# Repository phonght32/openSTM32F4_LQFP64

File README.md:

# openSTM32F4_LQFP64

### 1. Overview

Everything about this board: schematic, PCB gerber and BOM are free to distribute under open-source license for users.

The STM32F4 series chip inside openSTM32 board is based on ARM Cortex-M4 with floating point unit (FPU).

### 2. Specifications

| Items               | Specifications                                               |
| ------------------- | ------------------------------------------------------------ |
| Power supply        | 5V micro USB<br />5~36V Jack DC                              |
| Microcontroller     | STM32F405RGT6 / 32-bit ARM Cortex-M4 with FPU(168MHz, 225DMIPS) |
| Sensors             | 3 axis gyroscope, 3 axis accelerometer, 3 axis magnetometer (MPU9250) |
| Programmer          | JTAG/SWD connector<br />Serial (UART3)                       |
| Communicaton Ports  | UART x 3<br />I2C x 1<br />SPI x 1                           |
| Multimedia          | I2S x 1                                                      |
| Analog input        | ADC channel x 5                                              |
| Analog output       | DAC channel x 1                                              |
| PWM                 | Timer PWM x 4                                                |
| Leds and buttons    | D7 and D8: USB communication<br />D6: 3V3 power on<br />D1: USER LED status<br />SW2: Reset button<br />SW1: USER button |
| Digital I/O         | 10 pins                                                      |
| Output power source | 5V max 3A (TPS5430 step-down converter)<br />3V3 max 1A (AMS1117 linear regulator) |
| Dimensions          | 68 x 64 mm                                                   |

**NOTE:**

This board auto select power supply when both USB and jackDC are powered.

### 3. Layout / Pin map

### 4. Hardware design

#### Schematic

#### Dimension

#### PCB Top

#### PCB Bot

#### 3D Top

#### 3D Bot

### 5. Bill of Materials (BOM)

Download BOM [here.](assets/bom.xlsx)

### 6. Gerber

Download PCB gerber [here.](assets/openSTM32_68x54mm.zip)

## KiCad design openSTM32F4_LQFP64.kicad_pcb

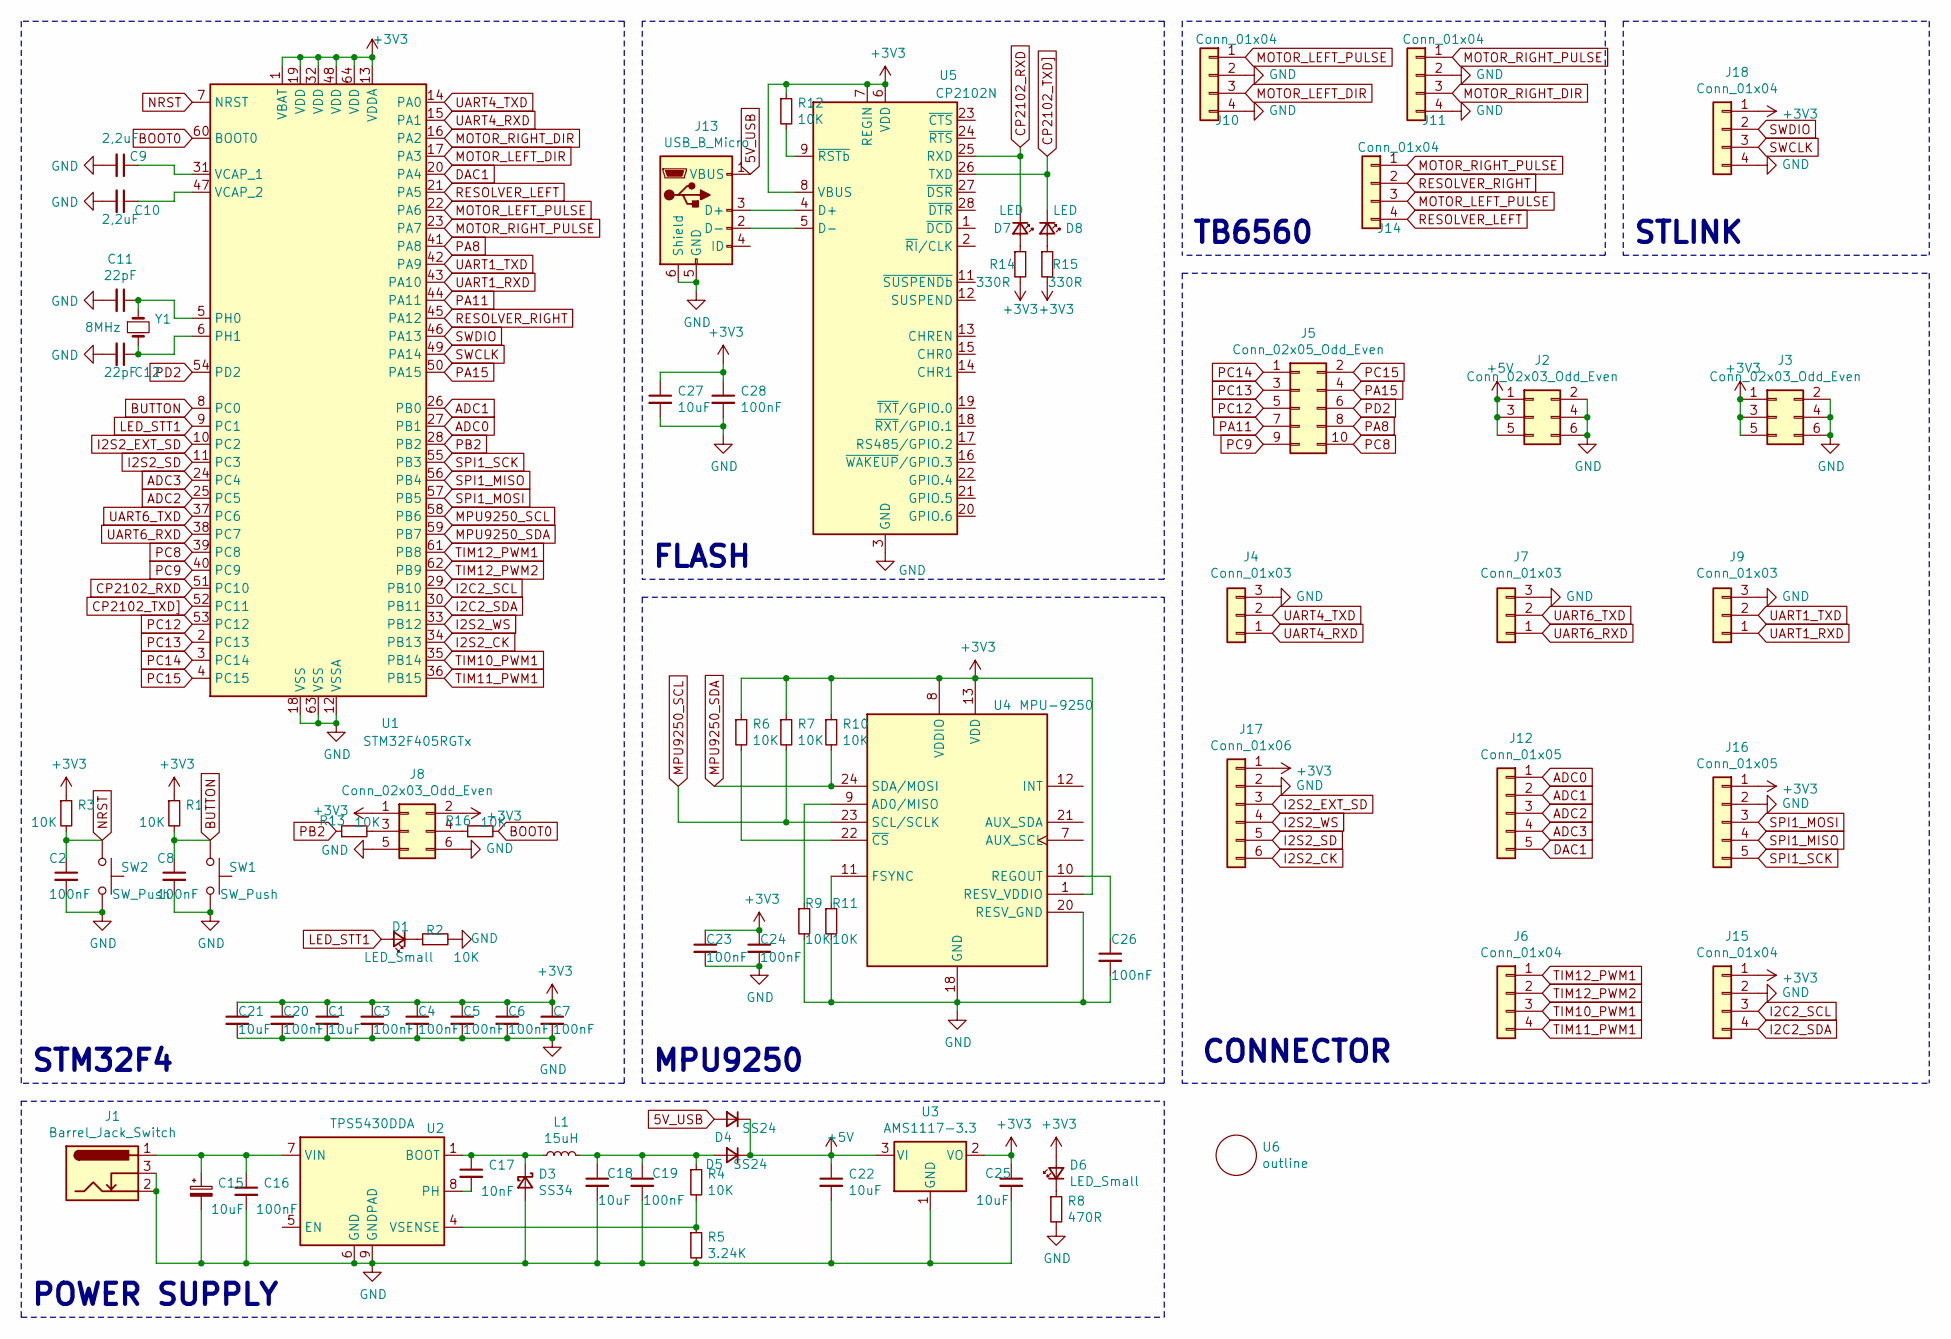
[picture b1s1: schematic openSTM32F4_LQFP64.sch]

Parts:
C1, C21, C22, C27: 10uF; C_0603_1608Metric_Pad1.05x0.95mm_HandSolder
C2, C3, C4, C5, C6, C7, C8, C16, C19, C20, C23, C24, C26, C28: 100nF; C_0603_1608Metric_Pad1.05x0.95mm_HandSolder
C9, C10: 2,2uF; C_0603_1608Metric_Pad1.05x0.95mm_HandSolder
C11, C12: 22pF; C_0603_1608Metric_Pad1.05x0.95mm_HandSolder
C15: 10uF; CP_Elec_8x10
C17: 10nF; C_0603_1608Metric_Pad1.05x0.95mm_HandSolder
C18, C25: 10uF; C_1210_3225Metric
D1, D6: LED_Small; LED_0603_1608Metric_Pad1.05x0.95mm_HandSolder
D3: SS34; D_SMA
D4, D5: SS24; D_SMA
D7, D8: LED; LED_0603_1608Metric_Pad1.05x0.95mm_HandSolder
J1: Barrel_Jack_Switch; BarrelJack_Wuerth_6941xx301002
J2, J3, J8: Conn_02x03_Odd_Even; PinHeader_2x03_P2.54mm_Vertical
J4, J7, J9: Conn_01x03; JST_EH_B3B-EH-A_1x03_P2.50mm_Vertical
J5: Conn_02x05_Odd_Even; PinHeader_2x05_P2.54mm_Vertical
J6, J10, J11, J15: Conn_01x04; JST_EH_B4B-EH-A_1x04_P2.50mm_Vertical
J12, J16: Conn_01x05; JST_EH_B5B-EH-A_1x05_P2.50mm_Vertical
J13: USB_B_Micro; USB_Micro-B_Wuerth_629105150521
J14, J18: Conn_01x04; PinHeader_1x04_P2.54mm_Vertical
J17: Conn_01x06; JST_EH_B6B-EH-A_1x06_P2.50mm_Vertical
L1: 15uH; L_12x12mm_H6mm
R1, R2, R3, R4, R6, R7, R9, R10, R11, R12, R13, R16: 10K; R_0603_1608Metric_Pad1.05x0.95mm_HandSolder
R5: 3.24K; R_0603_1608Metric_Pad1.05x0.95mm_HandSolder
R8: 470R; R_0603_1608Metric_Pad1.05x0.95mm_HandSolder
R14, R15: 330R; R_0603_1608Metric_Pad1.05x0.95mm_HandSolder
SW1, SW2: SW_Push; SW_Push_1P1T_NO_6x6mm_H9.5mm
U1: STM32F405RGTx; LQFP-64_10x10mm_P0.5mm
U2: TPS5430DDA; TI_SO-PowerPAD-8_ThermalVias
U3: AMS1117-3.3; SOT-223-3_TabPin2
U4: MPU-9250; MPU9250
U5: CP2102N; QFN-28-1EP_5x5mm_P0.5mm_EP3.35x3.35mm
U6: outline; openSTM32F4_LQFP64_outline
Y1: 8MHz; Crystal_HC49-4H_Vertical

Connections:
5V_USB: D4.2 (A), J13.1 (VBUS)
+3V3: C1.1, C3.1, C4.1, C5.1, C6.1, C7.1, C20.1, C21.1, C23.1, C24.1, C25.1, C27.1, C28.1, D6.2 (A), J3.1, J3.3, J3.5, J8.1, J8.2, J15.1, J16.1, J17.1, J18.1, R1.1, R3.1, R6.1, R7.1, R10.1, R12.1, R14.2, R15.2, U1.1 (VBAT), U1.13 (VDDA), U1.19 (VDD), U1.32 (VDD), U1.48 (VDD), U1.64 (VDD), U3.2 (VO), U4.1 (RESV_VDDIO), U4.8 (VDDIO), U4.13 (VDD), U5.6 (VDD), U5.7 (REGIN), U5.8 (VBUS)
+5V: C22.1, D4.1 (K), D5.1 (K), J2.1, J2.3, J2.5, U3.3 (VI)
ADC0: J12.1, U1.27 (PB1)
ADC1: J12.2, U1.26 (PB0)
ADC2: J12.3, U1.25 (PC5)
ADC3: J12.4, U1.24 (PC4)
BOOT0: R16.2, U1.60 (BOOT0)
BUTTON: C8.1, R1.2, SW1.1, U1.8 (PC0)
CP2102_RXD: D7.1 (K), U1.51 (PC10), U5.25 (RXD)
CP2102_TXD]: D8.1 (K), U1.52 (PC11), U5.26 (TXD)
DAC1: J12.5, U1.20 (PA4)
GND: C1.2, C2.2, C3.2, C4.2, C5.2, C6.2, C7.2, C8.2, C9.2, C10.2, C11.2, C12.2, C15.2, C16.2, C18.2, C19.2, C20.2, C21.2, C22.2, C23.2, C24.2, C25.2, C26.2, C27.2, C28.2, D3.2 (A), J1.2, J1.3, J2.2, J2.4, J2.6, J3.2, J3.4, J3.6, J4.3, J7.3, J8.5, J8.6, J9.3, J10.2, J10.4, J11.2, J11.4, J13.5 (GND), J13.6 (Shield), J15.2, J16.2, J17.2, J18.4, R2.2, R5.2, R8.2, R9.2, R11.2, SW1.2, SW2.2, U1.12 (VSSA), U1.18 (VSS), U1.63 (VSS), U2.6 (GND), U2.9 (GNDPAD), U3.1 (GND), U4.18 (GND), U4.20 (RESV_GND), U4.GND, U5.3 (GND), U5.29 (GND)
I2C2_SCL: J15.3, U1.29 (PB10)
I2C2_SDA: J15.4, U1.30 (PB11)
I2S2_CK: J17.6, U1.34 (PB13)
I2S2_EXT_SD: J17.3, U1.10 (PC2)
I2S2_SD: J17.5, U1.11 (PC3)
I2S2_WS: J17.4, U1.33 (PB12)
LED_STT1: D1.2 (A), U1.9 (PC1)
MOTOR_LEFT_DIR: J10.3, U1.17 (PA3)
MOTOR_LEFT_PULSE: J10.1, J14.3, U1.22 (PA6)
MOTOR_RIGHT_DIR: J11.3, U1.16 (PA2)
MOTOR_RIGHT_PULSE: J11.1, J14.1, U1.23 (PA7)
MPU9250_SCL: R7.2, U1.58 (PB6), U4.23 (SCL/SCLK)
MPU9250_SDA: R10.2, U1.59 (PB7), U4.24 (SDA/MOSI)
NRST: C2.1, R3.2, SW2.1, U1.7 (NRST)
unnamed: C9.1, U1.31 (VCAP_1)
unnamed: C10.1, U1.47 (VCAP_2)
unnamed: C11.1, U1.5 (PH0), Y1.1
unnamed: C12.1, U1.6 (PH1), Y1.2
unnamed: C15.1, C16.1, J1.1, U2.7 (VIN)
unnamed: C17.1, D3.1 (K), L1.1, U2.1 (BOOT)
unnamed: C17.2, U2.8 (PH)
unnamed: C18.1, C19.1, D5.2 (A), L1.2, R4.1
unnamed: C26.1, U4.10 (REGOUT)
unnamed: D1.1 (K), R2.1
unnamed: D6.1 (K), R8.1
unnamed: D7.2 (A), R14.1
unnamed: D8.2 (A), R15.1
unnamed: J8.3, R13.2
unnamed: J8.4, R16.1
unnamed: J13.2 (D-), U5.5 (D-)
unnamed: J13.3 (D+), U5.4 (D+)
unnamed: R4.2, R5.1, U2.4 (VSENSE)
unnamed: R6.2, U4.22 (~CS)
unnamed: R9.1, U4.9 (AD0/MISO)
unnamed: R11.1, U4.11 (FSYNC)
unnamed: R12.2, U5.9 (~RSTb)
PA8: J5.8, U1.41 (PA8)
PA11: J5.7, U1.44 (PA11)
PA15: J5.4, U1.50 (PA15)
PB2: R13.1, U1.28 (PB2)
PC8: J5.10, U1.39 (PC8)
PC9: J5.9, U1.40 (PC9)
PC12: J5.5, U1.53 (PC12)
PC13: J5.3, U1.2 (PC13)
PC14: J5.1, U1.3 (PC14)
PC15: J5.2, U1.4 (PC15)
PD2: J5.6, U1.54 (PD2)
RESOLVER_LEFT: J14.4, U1.21 (PA5)
RESOLVER_RIGHT: J14.2, U1.45 (PA12)
SPI1_MISO: J16.4, U1.56 (PB4)
SPI1_MOSI: J16.3, U1.57 (PB5)
SPI1_SCK: J16.5, U1.55 (PB3)
SWCLK: J18.3, U1.49 (PA14)
SWDIO: J18.2, U1.46 (PA13)
TIM10_PWM1: J6.3, U1.35 (PB14)
TIM11_PWM1: J6.4, U1.36 (PB15)
TIM12_PWM1: J6.1, U1.61 (PB8)
TIM12_PWM2: J6.2, U1.62 (PB9)
UART1_RXD: J9.1, U1.43 (PA10)
UART1_TXD: J9.2, U1.42 (PA9)
UART4_RXD: J4.1, U1.15 (PA1)
UART4_TXD: J4.2, U1.14 (PA0)
UART6_RXD: J7.1, U1.38 (PC7)
UART6_TXD: J7.2, U1.37 (PC6)

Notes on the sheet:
STM32F4
FLASH
MPU9250
POWER SUPPLY
TB6560
CONNECTOR
STLINK

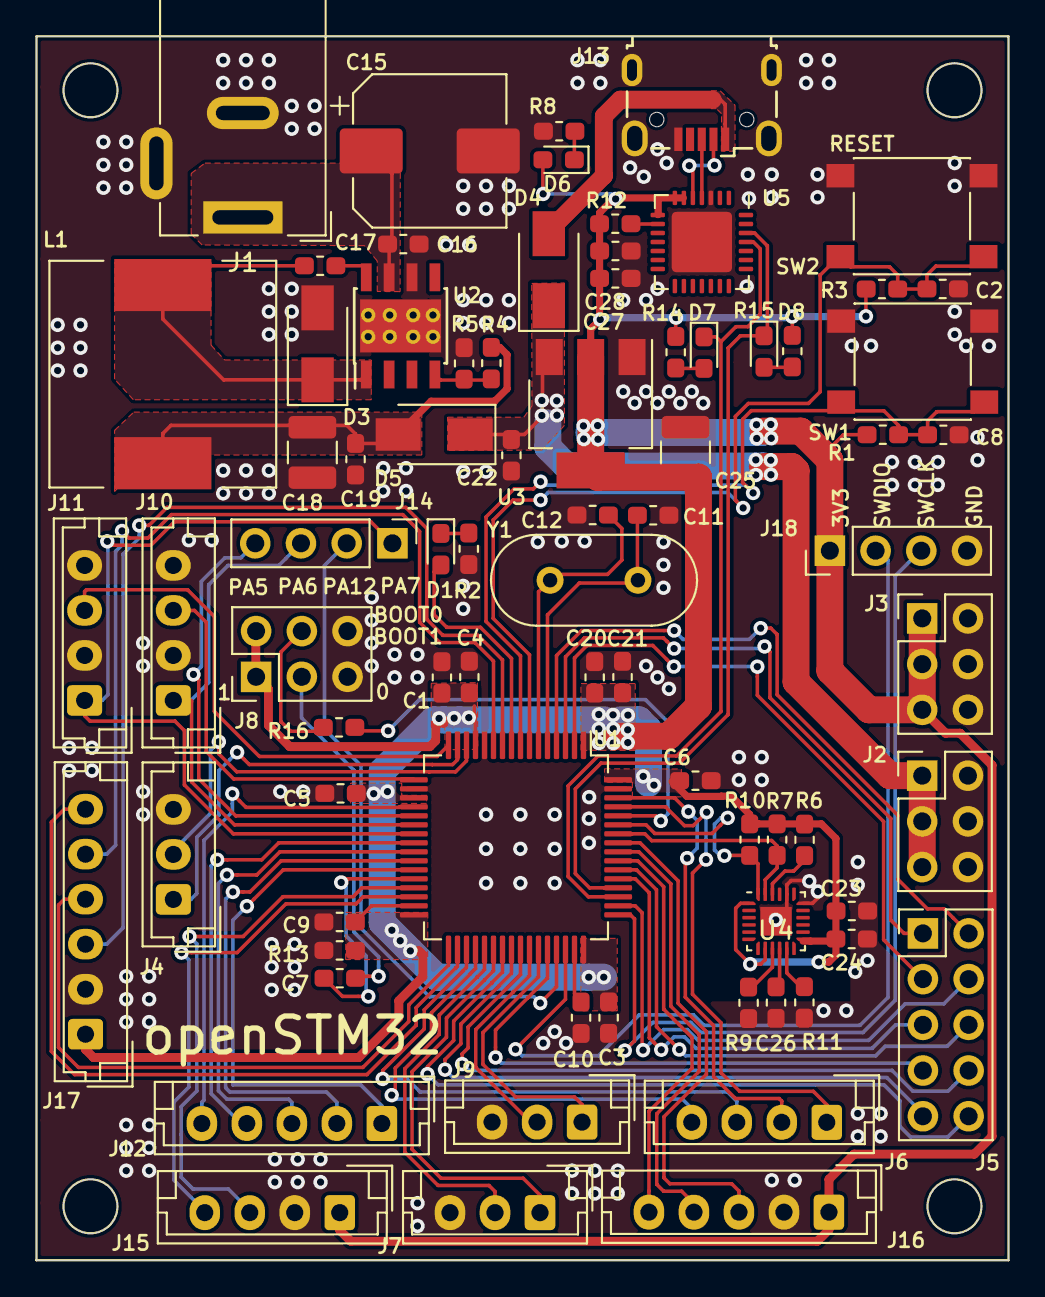
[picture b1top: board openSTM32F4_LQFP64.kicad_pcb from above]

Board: 2 copper layers, 54.0 x 68.0 mm, 77 parts (0 on the bottom side), 77 nets.

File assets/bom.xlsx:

Source: | /home/phong/Documents/thesis/openSTM32F4_LQFP64/openSTM32F4_LQFP64.sch
Date: | Thứ bảy, 23 Tháng năm Năm 2020 22:04:47 +07
Tool: | Eeschema 5.1.6-c6e7f7d~86~ubuntu16.04.1
Generator: | /usr/share/kicad/plugins/bom_csv_grouped_by_value_with_fp.py
Component Count: | 77
Ref | Qnty | Value | Cmp name | Footprint | Description | Vendor
C1, C21, C22, C27, | 4 | 10uF | C_Small | Capacitor_SMD:C_0603_1608Metric_Pad1.05x0.95mm_HandSolder | Unpolarized capacitor, small symbol
C2, C3, C4, C5, C6, C7, C8, C16, C19, C20, C23, C24, C26, C28, | 14 | 100nF | C_Small | Capacitor_SMD:C_0603_1608Metric_Pad1.05x0.95mm_HandSolder | Unpolarized capacitor, small symbol
C9, C10, | 2 | 2,2uF | C_Small | Capacitor_SMD:C_0603_1608Metric_Pad1.05x0.95mm_HandSolder | Unpolarized capacitor, small symbol
C11, C12, | 2 | 22pF | C_Small | Capacitor_SMD:C_0603_1608Metric_Pad1.05x0.95mm_HandSolder | Unpolarized capacitor, small symbol
C15, | 1 | 10uF | CP_Small | Capacitor_SMD:CP_Elec_8x10 | Polarized capacitor, small symbol
C17, | 1 | 10nF | C_Small | Capacitor_SMD:C_0603_1608Metric_Pad1.05x0.95mm_HandSolder | Unpolarized capacitor, small symbol
C18, C25, | 2 | 10uF | C_Small | Capacitor_SMD:C_1210_3225Metric | Unpolarized capacitor, small symbol
D1, D6, | 2 | LED_Small | LED_Small | LED_SMD:LED_0603_1608Metric_Pad1.05x0.95mm_HandSolder | Light emitting diode, small symbol
D3, | 1 | SS34 | D_Schottky_Small | Diode_SMD:D_SMA | Schottky diode, small symbol
D4, D5, | 2 | SS24 | D_Small | Diode_SMD:D_SMA | Diode, small symbol
D7, D8, | 2 | LED | LED_Small | LED_SMD:LED_0603_1608Metric_Pad1.05x0.95mm_HandSolder | Light emitting diode, small symbol
J1, | 1 | Barrel_Jack_Switch | Barrel_Jack_Switch | Connector_BarrelJack:BarrelJack_Wuerth_6941xx301002 | DC Barrel Jack with an internal switch
J2, J3, J8, | 3 | Conn_02x03_Odd_Even | Conn_02x03_Odd_Even | Connector_PinHeader_2.54mm:PinHeader_2x03_P2.54mm_Vertical | Generic connector, double row, 02x03, odd/even pin numbering scheme (row 1 odd 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
J4, J7, J9, | 3 | Conn_01x03 | Conn_01x03 | Connector_JST:JST_EH_B3B-EH-A_1x03_P2.50mm_Vertical | Generic connector, single row, 01x03, script generated (kicad-library-utils/sch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
J5, | 1 | Conn_02x05_Odd_Even | Conn_02x05_Odd_Even | Connector_PinHeader_2.54mm:PinHeader_2x05_P2.54mm_Vertical | Generic connector, double row, 02x05, odd/even pin numbering scheme (row 1 odd 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
J6, J10, J11, J15, | 4 | Conn_01x04 | Conn_01x04 | Connector_JST:JST_EH_B4B-EH-A_1x04_P2.50mm_Vertical | Generic connector, single row, 01x04, script generated (kicad-library-utils/sch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
J12, J16, | 2 | Conn_01x05 | Conn_01x05 | Connector_JST:JST_EH_B5B-EH-A_1x05_P2.50mm_Vertical | Generic connector, single row, 01x05, script generated (kicad-library-utils/sch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
J13, | 1 | USB_B_Micro | USB_B_Micro | Connector_USB:USB_Micro-B_Wuerth_629105150521 | USB Micro Type B connector
J14, J18, | 2 | Conn_01x04 | Conn_01x04 | Connector_PinHeader_2.54mm:PinHeader_1x04_P2.54mm_Vertical | Generic connector, single row, 01x04, script generated (kicad-library-utils/sch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
J17, | 1 | Conn_01x06 | Conn_01x06 | Connector_JST:JST_EH_B6B-EH-A_1x06_P2.50mm_Vertical | Generic connector, single row, 01x06, script generated (kicad-library-utils/sch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
L1, | 1 | 15uH | L_Small | Inductor_SMD:L_12x12mm_H6mm | Inductor, small symbol
R1, R2, R3, R4, R6, R7, R9, R10, R11, R12, R13, R16, | 12 | 10K | R_Small | Resistor_SMD:R_0603_1608Metric_Pad1.05x0.95mm_HandSolder | Resistor, small symbol
R5, | 1 | 3.24K | R_Small | Resistor_SMD:R_0603_1608Metric_Pad1.05x0.95mm_HandSolder | Resistor, small symbol
R8, | 1 | 470R | R_Small | Resistor_SMD:R_0603_1608Metric_Pad1.05x0.95mm_HandSolder | Resistor, small symbol
R14, R15, | 2 | 330R | R_Small | Resistor_SMD:R_0603_1608Metric_Pad1.05x0.95mm_HandSolder | Resistor, small symbol
SW1, SW2, | 2 | SW_Push | SW_Push | Button_Switch_SMD:SW_Push_1P1T_NO_6x6mm_H9.5mm | Push button switch, generic, two pins
U1, | 1 | STM32F405RGTx | STM32F405RGTx | Package_QFP:LQFP-64_10x10mm_P0.5mm | ARM Cortex-M4 MCU, 1024KB flash, 128KB RAM, 168MHz, 1.8-3.6V, 51 GPIO, LQFP-64
U2, | 1 | TPS5430DDA | TPS5430DDA | Package_SO:TI_SO-PowerPAD-8_ThermalVias | 3A, Step Down Swift Converter, Adjustable Output Voltage, 5.5-36V Input Voltage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
U3, | 1 | AMS1117-3.3 | AMS1117-3.3 | Package_TO_SOT_SMD:SOT-223-3_TabPin2 | 1A Low Dropout regulator, positive, 3.3V fixed output, SOT-223
U4, | 1 | MPU-9250 | MPU-9250 | Sensor_Motion:InvenSense_QFN-24_3x3mm_P0.4mm | InvenSense 9-Axis Motion Sensor, Accelerometer, Gyroscope, Compass, I2C/SPI
U5, | 1 | CP2102N | CP2102N-A01-GQFN28 | Package_DFN_QFN:QFN-28-1EP_5x5mm_P0.5mm_EP3.35x3.35mm | USB to UART master bridge, QFN-28
U6, | 1 | outline | outline | footprints:openSTM32F4_LQFP64_outline
Y1, | 1 | 8MHz | Crystal_Small | Crystal:Crystal_HC49-4H_Vertical | Two pin crystal, small symbol

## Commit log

2020-04-25 update library
2020-04-25 update jackDC mounting pin
2020-04-25 update gnd via
2020-05-16 update gerber
2020-05-18 update via size
2020-05-23 update 3d view
2020-05-23 add bom
2020-05-23 add documents
2020-05-31 add mpu9250 footprint
2020-05-31 fix mpu9250 thermal pad
2020-06-01 update mpu9250 footprint
2020-07-19 update hardware
2020-07-29 update project
2023-01-11 Update LICENSE
